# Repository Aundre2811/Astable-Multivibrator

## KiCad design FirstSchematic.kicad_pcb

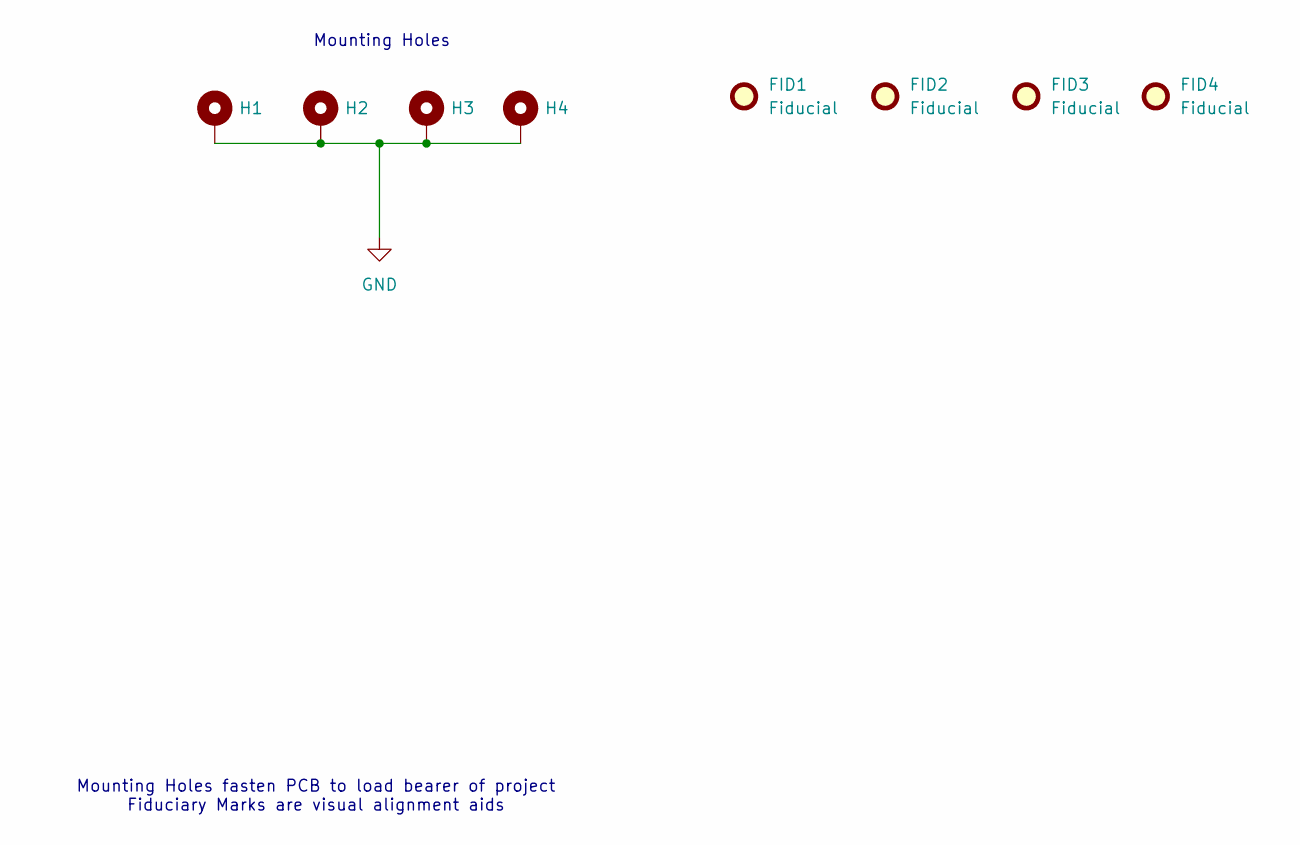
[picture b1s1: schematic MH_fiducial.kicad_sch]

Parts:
FID1, FID2, FID3, FID4: Fiducial; Fiducial_1.5mm_Mask3mm
H1, H2, H3, H4: MountingHole_Pad; MountingHole_2.5mm_Pad

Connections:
GND: H1.1 (1_1), H2.1 (1_1), H3.1 (1_1), H4.1 (1_1); also elsewhere on the board

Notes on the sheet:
Mounting Holes fasten PCB to load bearer of project Fiduciary Marks are visual alignment aids
Mounting Holes

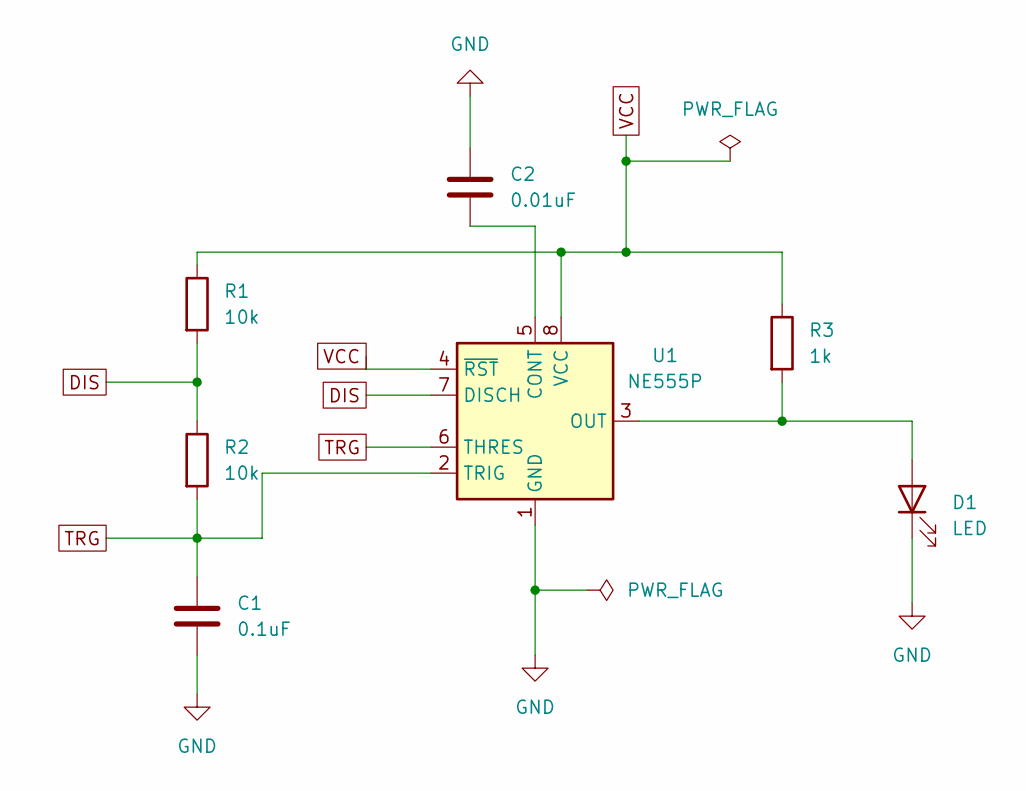
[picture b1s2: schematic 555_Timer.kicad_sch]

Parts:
C1: 0.1uF; C_0603_1608Metric
C2: 0.01uF; C_0603_1608Metric
D1: LED; LED_0603_1608Metric
R1, R2: 10k; R_0603_1608Metric
R3: 1k; R_0603_1608Metric
U1: NE555P; SOP-8_3.76x4.96mm_P1.27mm

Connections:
DIS: R1.2, R2.1, U1.7 (DISCH)
GND: C1.2, C2.1, D1.1 (K), U1.1 (GND); also elsewhere on the board
unnamed: D1.2 (A), R3.2, U1.3 (OUT)
unnamed: C2.2, U1.5 (CONT)
TRG: C1.1, R2.2, U1.2 (TRIG), U1.6 (THRES)
VCC: R1.1, R3.1, U1.4 (~RST), U1.8 (VCC); also elsewhere on the board

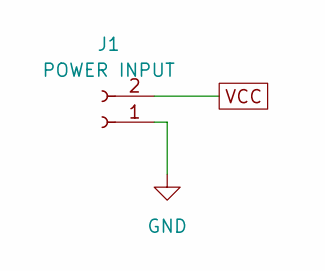
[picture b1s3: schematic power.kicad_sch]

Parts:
J1: POWER INPUT; PinHeader_1x02_P2.54mm_Vertical

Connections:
GND: J1.1; also elsewhere on the board
VCC: J1.2; also elsewhere on the board

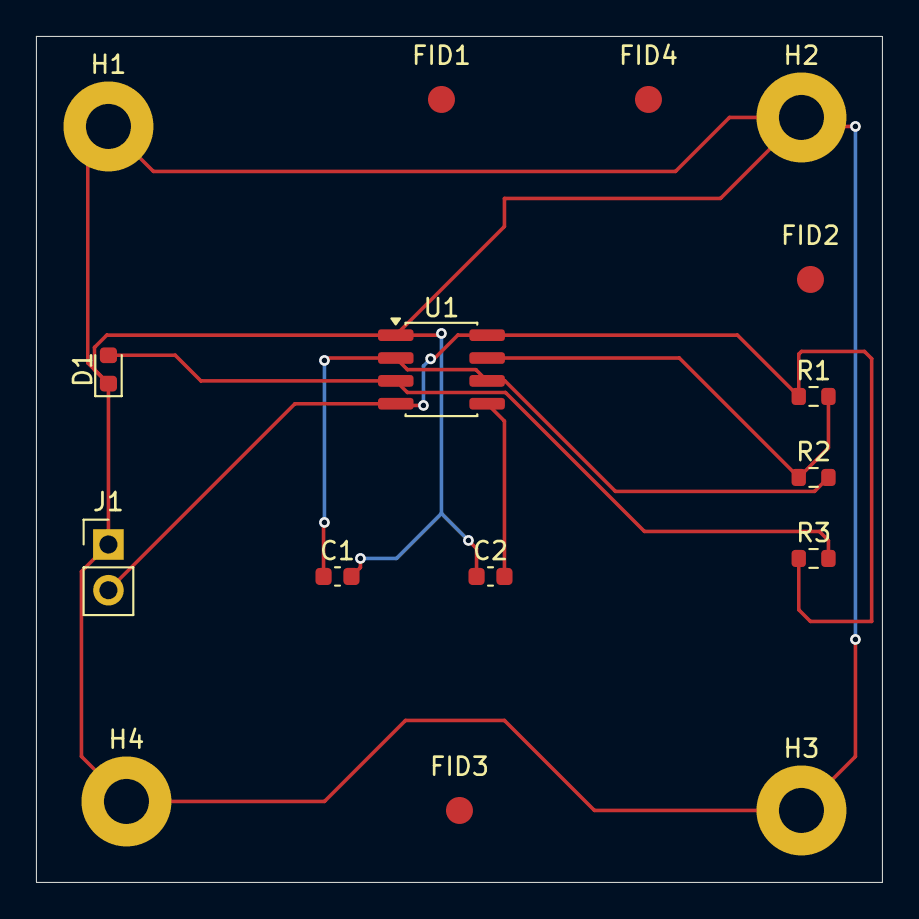
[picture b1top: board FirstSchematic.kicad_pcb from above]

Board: 2 copper layers, 47.0 x 47.0 mm, 16 parts (0 on the bottom side), 6 nets.

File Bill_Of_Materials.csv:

Reference,Qty,Value,DNP,Exclude from BOM,Exclude from Board,Footprint,Datasheet
C1,1,0.1uF,,,,Capacitor_SMD:C_0603_1608Metric,
C2,1,0.01uF,,,,Capacitor_SMD:C_0603_1608Metric,
D1,1,LED,,,,LED_SMD:LED_0603_1608Metric,
J1,1,POWER INPUT,,,,Connector_PinHeader_2.54mm:PinHeader_1x02_P2.54mm_Vertical,
"R1,R2",2,10k,,,,Resistor_SMD:R_0603_1608Metric,
R3,1,1k,,,,Resistor_SMD:R_0603_1608Metric,
U1,1,NE555P,,,,Package_SO:SOP-8_3.76x4.96mm_P1.27mm,http://www.ti.com/lit/ds/symlink/ne555.pdf
